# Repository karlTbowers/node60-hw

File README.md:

# Node60 — Automotive 10BASE-T1S Power Distribution Node

Open-hardware six-output automotive power distribution node by DropOut. Each output is a protected smart high-side switch with current and voltage telemetry, reported over a multidrop 10BASE-T1S network.

**Status:** Architecture Rev A, schematic capture starting. Not yet validated hardware.

**Architecture and design documentation:** https://karltbowers.github.io/node60-hw/ (source in [`docs/`](docs/)).

| | |
|---|---|
| MCU | NXP S32K344 |
| Network | Microchip LAN8670 10BASE-T1S PHY (RMII), PLCA follower |
| Outputs | 6 × 10 A target, 3 × TI TPS2HCS08A-Q1 dual smart eFuses |
| Input | 12 V battery-direct, TI LM74910H-Q1 ideal diode + 75 A breaker |
| Tools | KiCad 10, Zephyr RTOS (firmware in a separate repo) |

## Cloning

The DropOut part library is a git submodule, so clone recursively:

```bash
git clone --recursive https://github.com/karlTbowers/node60-hw.git
```

Already cloned without it? Run `git submodule update --init`.

## Workstation

To set up a new Apple-silicon Mac with the whole design environment, run `scripts/setup-workstation.sh`. It installs KiCad 10.0.7, the Homebrew tools, the DropOut repos, KiCadRoutingTools and its Python, then checks that the Mac reproduces the reference judging run. See [`scripts/workstation/README.md`](scripts/workstation/README.md).

## Layout

```
node60.kicad_pro / .kicad_sch / .kicad_pcb    KiCad 10 project; node60.kicad_sch is the root sheet (page 1, index)
sheets/                                       every other schematic sheet, flat (handbook ch. 05)
scripts/check_schematic.py                    CI check: sheet files, page numbers, reference designators
sym-lib-table, fp-lib-table                   point into lib/ — do not use global DropOut tables
lib/dropout-kicad-library/                    submodule: symbols, footprints, 3D models
docs/                                         Starlight documentation site: architecture, calculations, test plans
.github/workflows/ci.yml                      ERC/DRC on every push; fab outputs on tags
.github/workflows/docs.yml                    builds docs/ on PRs; deploys main to GitHub Pages
```

## Library

All parts come from [dropout-kicad-library](https://github.com/karlTbowers/dropout-kicad-library). The project library tables use `${KIPRJMOD}/lib/dropout-kicad-library/...`, so nothing needs to be configured in KiCad's global settings.

Update the library:

```bash
git -C lib/dropout-kicad-library pull origin main
git add lib/dropout-kicad-library
git commit -m "Update DropOut library"
```

## Releases

Board revisions are git tags: `rev-a`, `rev-b`, … Pushing a tag makes CI run ERC and DRC and attach the fabrication package (Gerbers, drill, position file, BOM, schematic PDF) to a GitHub Release.

```bash
git tag rev-a && git push origin rev-a
```

## License

TBD — to be chosen before the first public release.

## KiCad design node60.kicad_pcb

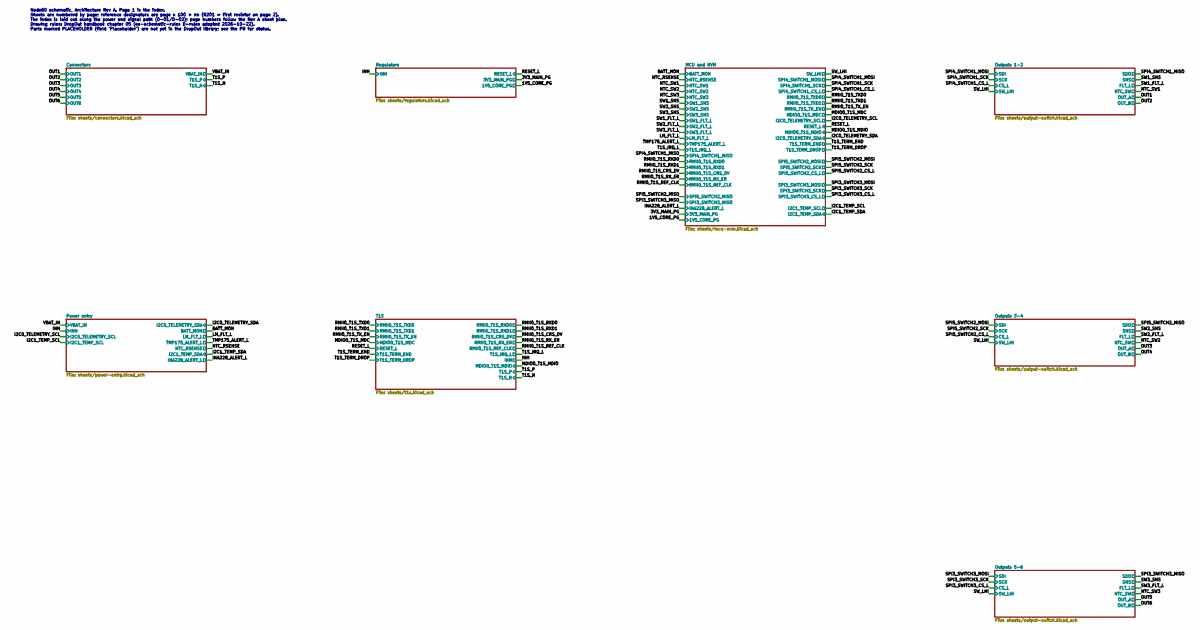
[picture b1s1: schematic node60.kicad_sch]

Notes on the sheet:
Node60 schematic, Architecture Rev A. Page 1 is the index. Sheets are numbered by page; reference designators are page x 100 + nn (R201 = first resistor on page 2). The index is laid out along the power and signal path (D-01/D-02); page numbers follow the Rev A sheet plan. Drawing rules: DropOut ha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

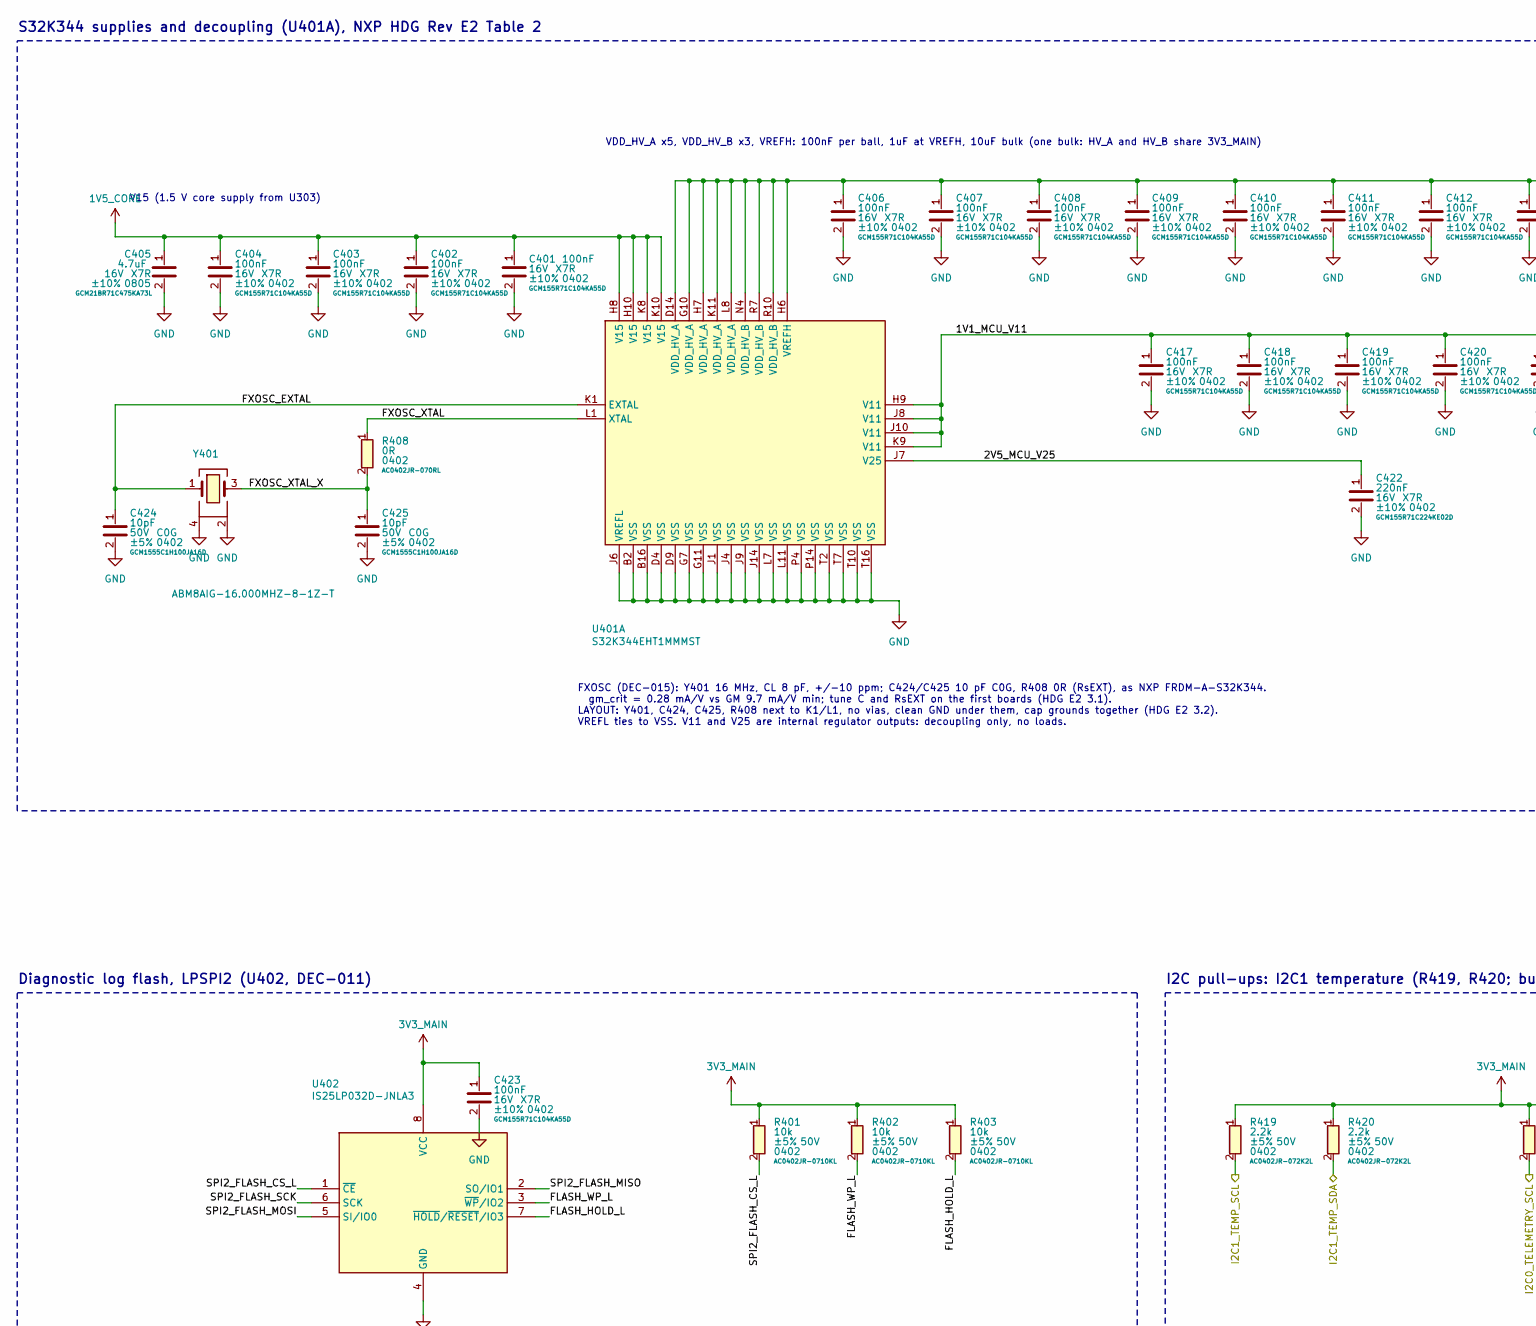
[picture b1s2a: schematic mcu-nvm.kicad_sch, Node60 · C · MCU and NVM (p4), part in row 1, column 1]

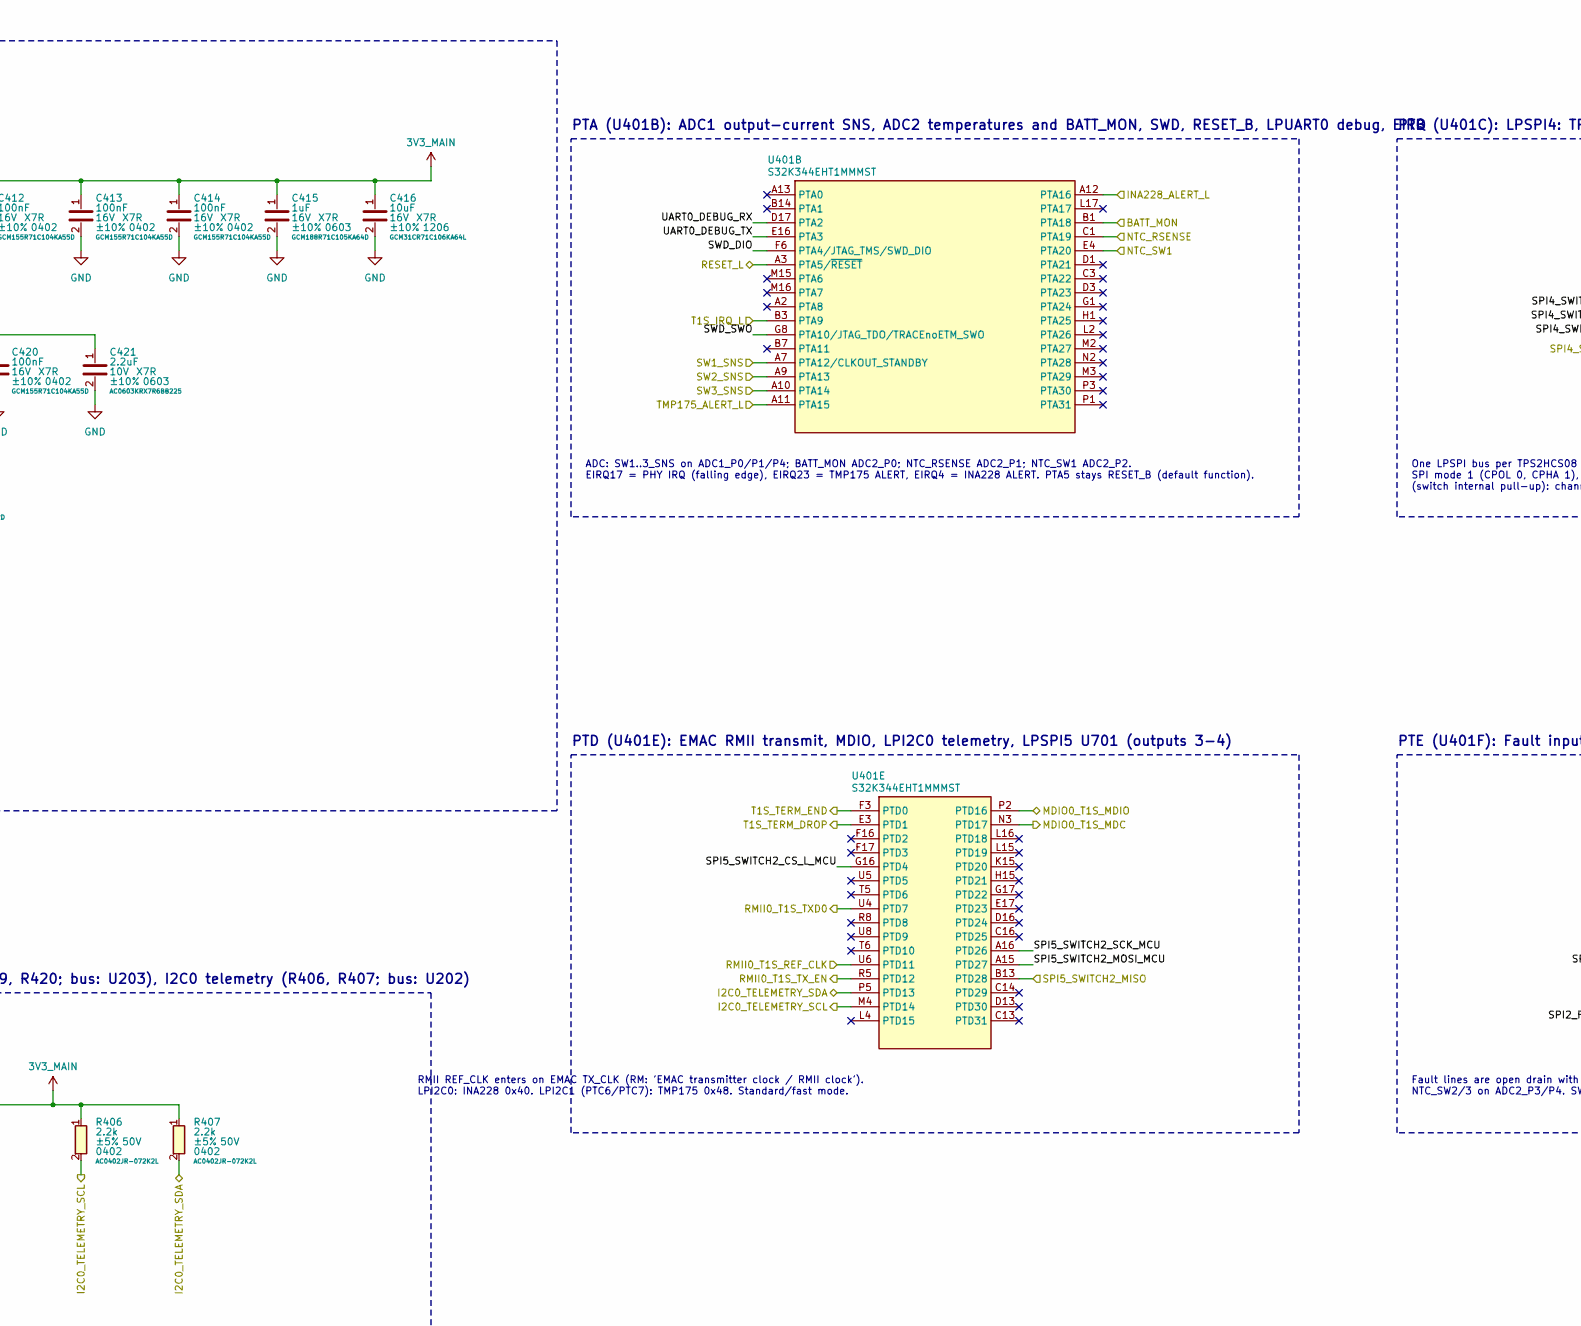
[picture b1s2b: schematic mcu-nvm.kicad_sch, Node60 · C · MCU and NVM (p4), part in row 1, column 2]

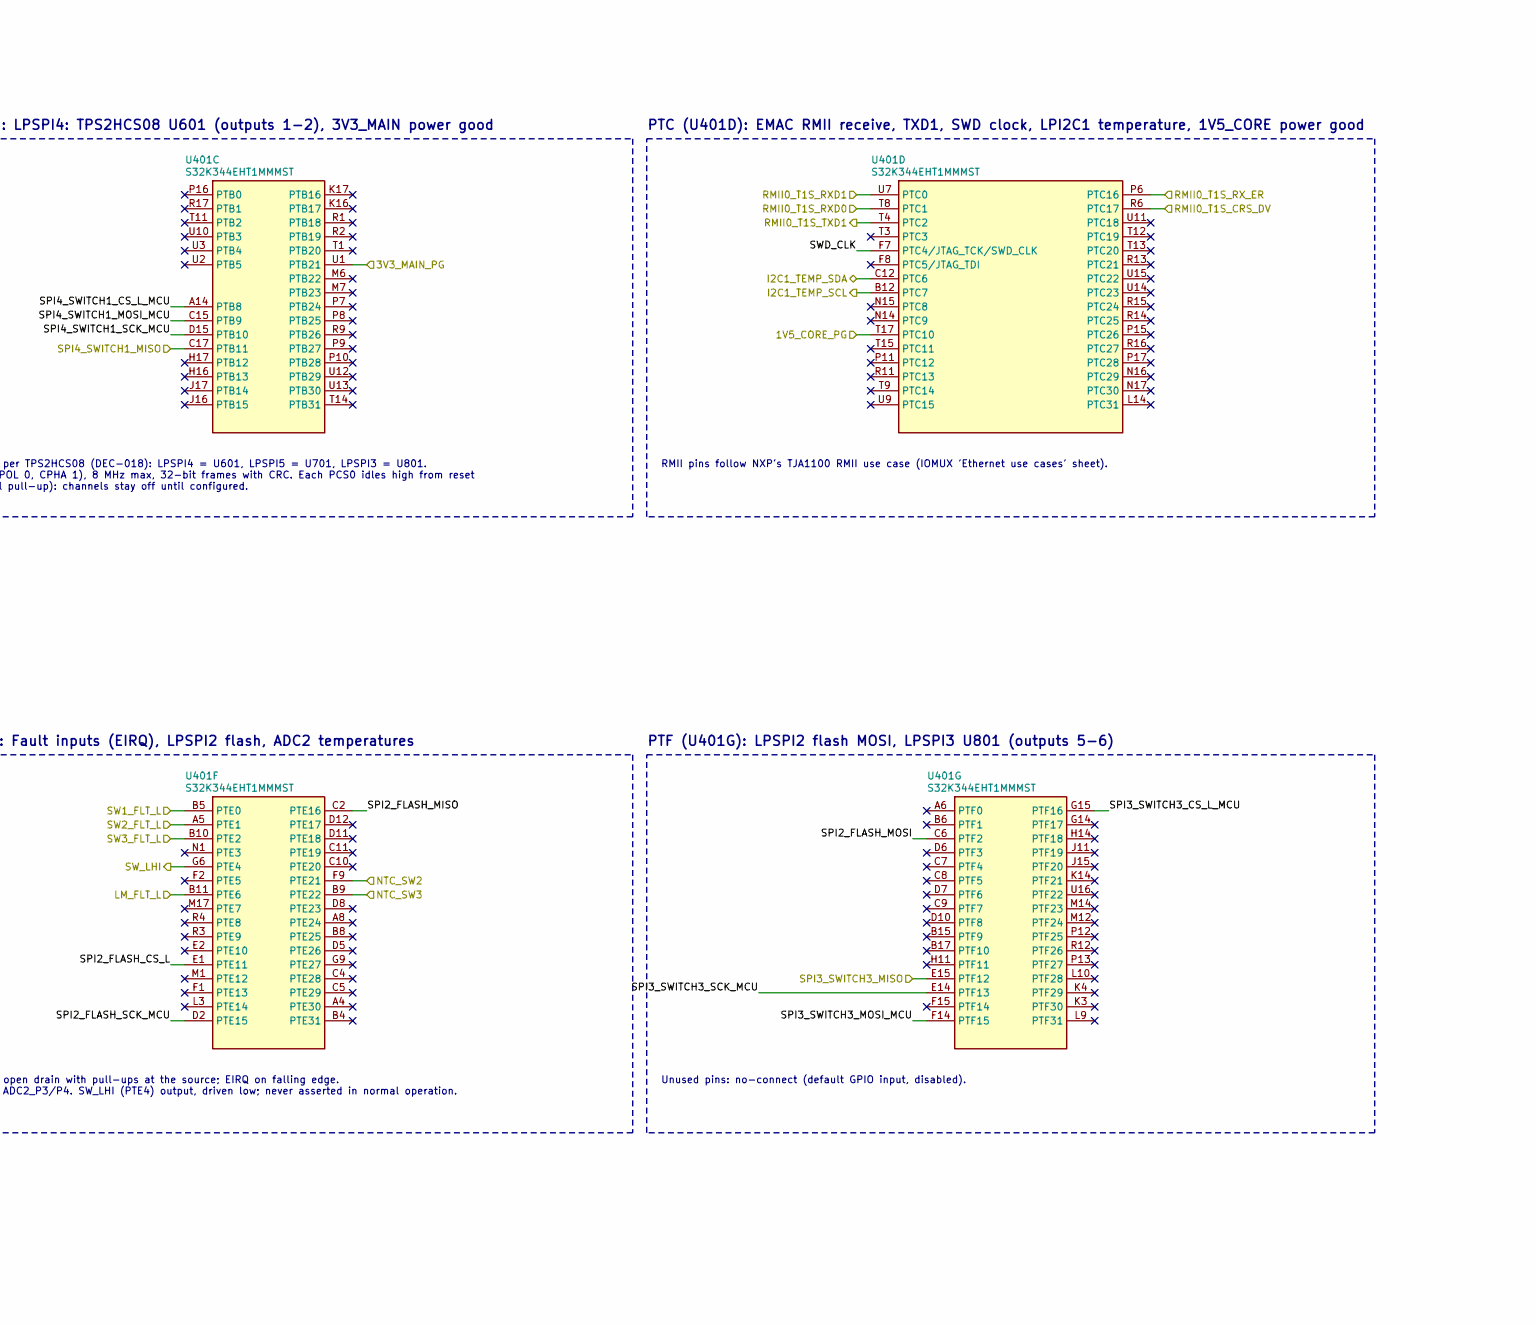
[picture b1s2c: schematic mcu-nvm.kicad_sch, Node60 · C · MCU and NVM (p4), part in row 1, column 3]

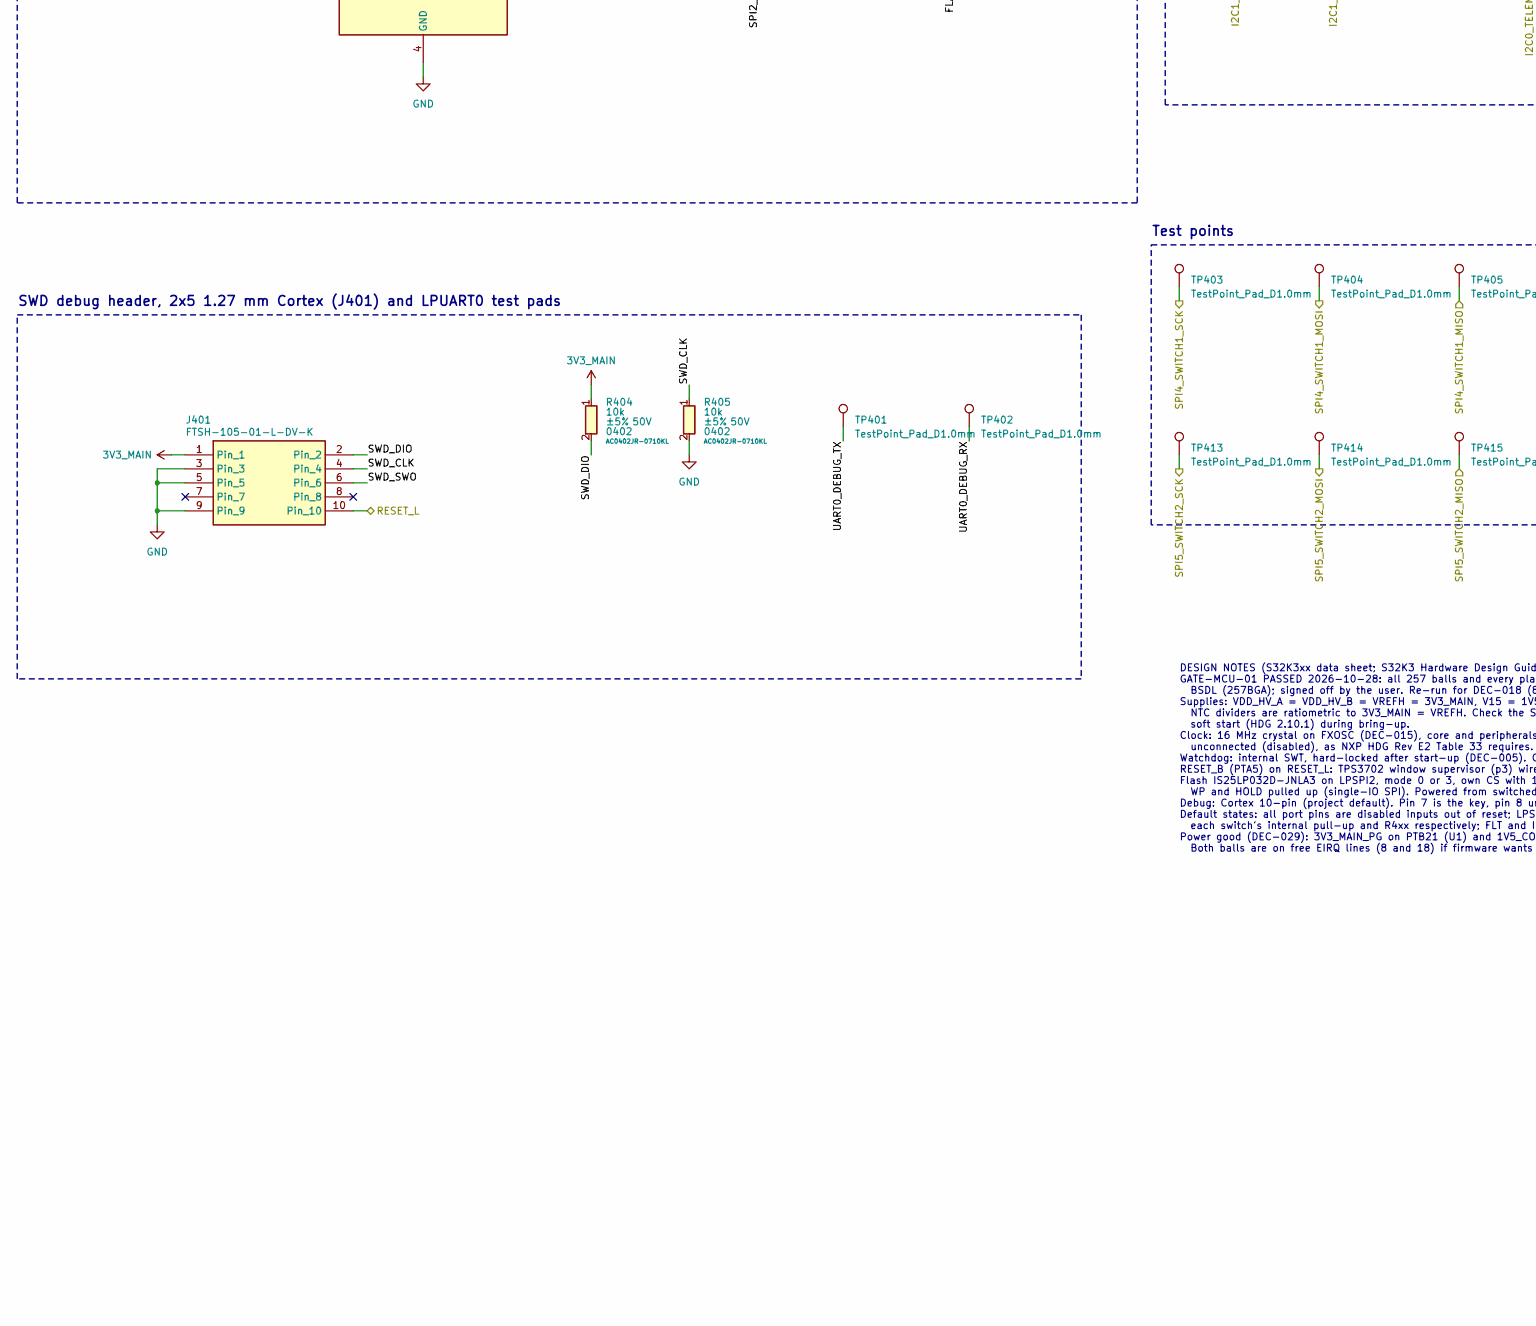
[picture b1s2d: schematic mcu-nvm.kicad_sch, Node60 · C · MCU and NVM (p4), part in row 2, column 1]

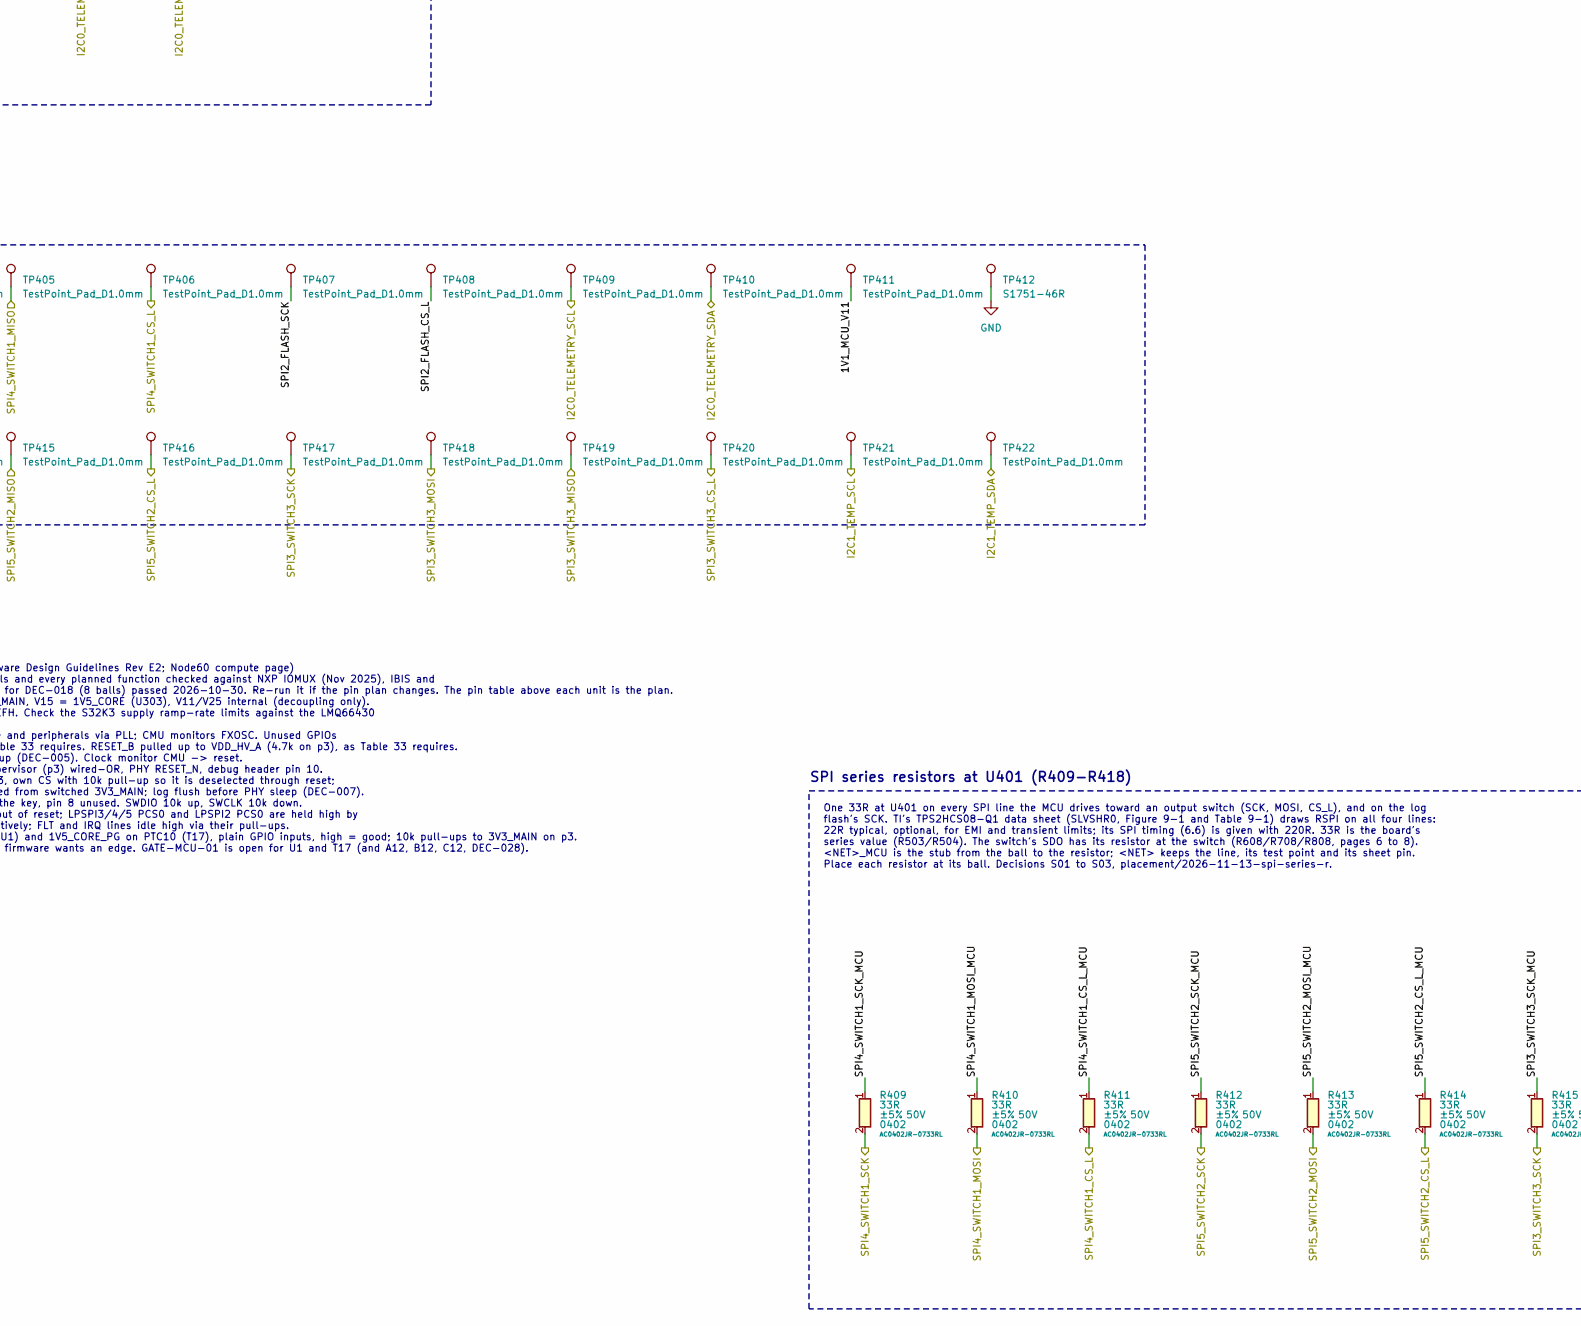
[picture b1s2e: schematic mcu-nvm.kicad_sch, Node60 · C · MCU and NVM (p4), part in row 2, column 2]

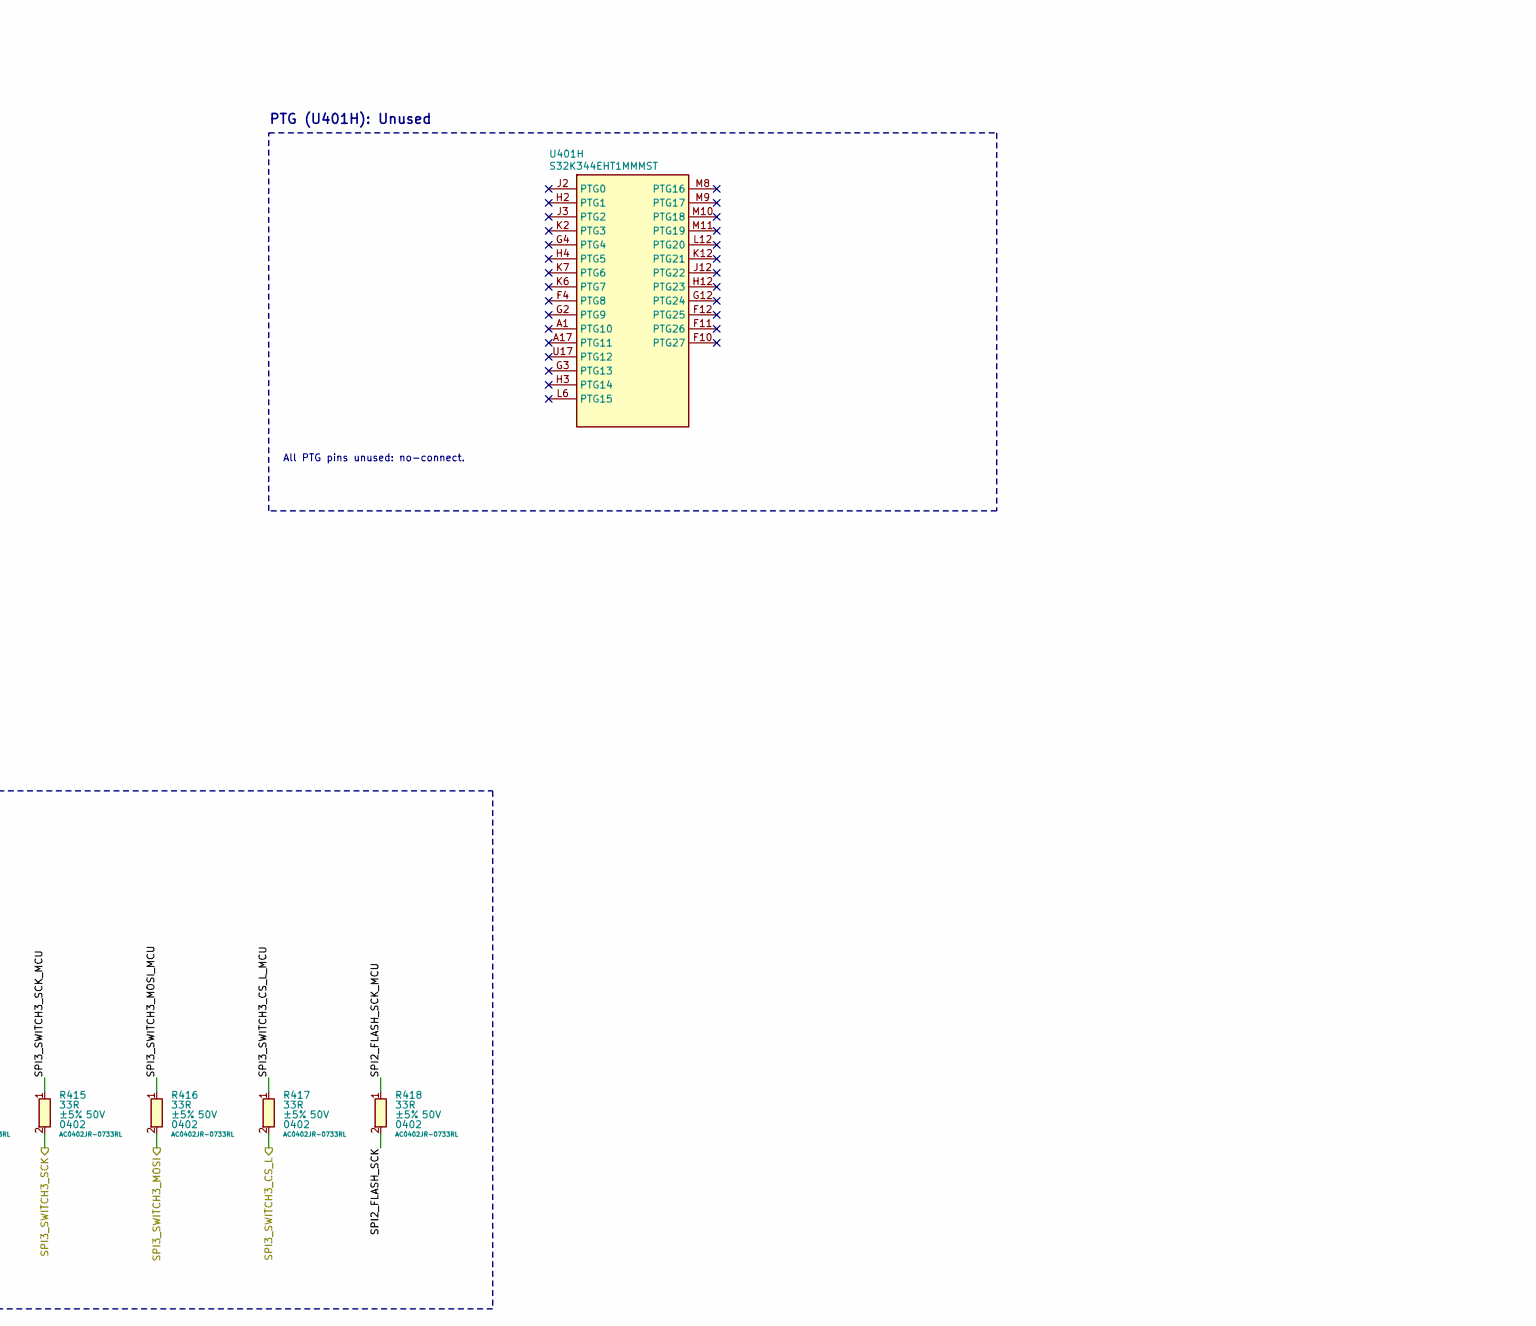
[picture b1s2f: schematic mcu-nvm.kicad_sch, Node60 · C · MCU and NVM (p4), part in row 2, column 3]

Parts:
C401, C402, C403, C404, C406, C407, C408, C409, C410, C411, C412, C413, C414, C417, C418, C419, C420, C423: 100nF; C_0402_1005Metric; Voltage 16V; Tolerance ±10%; MPN GCM155R71C104KA55D; DigiKey_PN 490-4759-1-ND
C405: 4.7uF; C_0805_2012Metric; Voltage 16V; Tolerance ±10%; MPN GCM21BR71C475KA73L; DigiKey_PN 490-5332-1-ND
C415: 1uF; C_0603_1608Metric; Voltage 16V; Tolerance ±10%; MPN GCM188R71C105KA64D; DigiKey_PN 490-5241-1-ND
C416: 10uF; C_1206_3216Metric; Voltage 16V; Tolerance ±10%; MPN GCM31CR71C106KA64L; DigiKey_PN 490-4793-1-ND
C421: 2.2uF; C_0603_1608Metric; Voltage 10V; Tolerance ±10%; MPN AC0603KRX7R6BB225; DigiKey_PN 13-AC0603KRX7R6BB225CT-ND
C422: 220nF; C_0402_1005Metric; Voltage 16V; Tolerance ±10%; MPN GCM155R71C224KE02D; DigiKey_PN 490-10671-1-ND
C424, C425: 10pF; C_0402_1005Metric; Voltage 50V; Tolerance ±5%; MPN GCM1555C1H100JA16D; DigiKey_PN 490-10668-1-ND
J401: FTSH-105-01-L-DV-K; Samtec_FTSH-105-01-x-DV_2x05_P1.27mm_Vertical_SMD; MPN FTSH-105-01-L-DV-K; DigiKey_PN SAM8799-ND
R401, R402, R403, R404, R405: 10k; R_0402_1005Metric; Tolerance ±5%; Voltage 50V; MPN AC0402JR-0710KL; DigiKey_PN YAG3517CT-ND
R406, R407, R419, R420: 2.2k; R_0402_1005Metric; Tolerance ±5%; Voltage 50V; MPN AC0402JR-072K2L; DigiKey_PN YAG3536CT-ND
R408: 0R; R_0402_1005Metric; MPN AC0402JR-070RL; DigiKey_PN 311-0.0LBCT-ND
R409, R410, R411, R412, R413, R414, R415, R416, R417, R418: 33R; R_0402_1005Metric; Tolerance ±5%; Voltage 50V; MPN AC0402JR-0733RL; DigiKey_PN YAG3543CT-ND
TP401, TP402, TP403, TP404, TP405, TP406, TP407, TP408, TP409, TP410, TP411, TP413, TP414, TP415, TP416, TP417, TP418, TP419, TP420, TP421, TP422: TestPoint_Pad_D1.0mm; MPN TestPoint_Pad_D1.0mm
TP412: S1751-46R; TestPoint_Harwin_S1751; MPN S1751-46R; DigiKey_PN 952-1478-1-ND
U401: S32K344EHT1MMMST; NXP_LFBGA-257_14x14mm_Layout17x17_P0.8mm; MPN S32K344EHT1MMMST; DigiKey_PN 568-S32K344EHT1MMMST-ND
U402: IS25LP032D-JNLA3; SOIC-8_3.9x4.9mm_P1.27mm; MPN IS25LP032D-JNLA3; DigiKey_PN 706-IS25LP032D-JNLA3-ND
Y401: ABM8AIG-16.000MHZ-8-1Z-T; Crystal_SMD_NDK_NX3225SA-4Pin_3.2x2.5mm; MPN ABM8AIG-16.000MHZ-8-1Z-T; DigiKey_PN 535-ABM8AIG-16.000MHZ-8-1Z-TCT-ND

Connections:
1V5_CORE: C401.1, C402.1, C403.1, C404.1, C405.1, U401.H8 (V15), U401.H10 (V15), U401.K8 (V15), U401.K10 (V15); also elsewhere on the board
3V3_MAIN: C406.1, C407.1, C408.1, C409.1, C410.1, C411.1, C412.1, C413.1, C414.1, C415.1, C416.1, C423.1, J401.1, R401.1, R402.1, R403.1, R404.1, R406.1, R407.1, R419.1, R420.1, U401.D14 (VDD_HV_A), U401.G10 (VDD_HV_A), U401.H6 (VREFH), U401.H7 (VDD_HV_A), U401.K11 (VDD_HV_A), U401.L8 (VDD_HV_A), U401.N4 (VDD_HV_B), U401.R7 (VDD_HV_B), U401.R10 (VDD_HV_B), U402.8 (VCC); also elsewhere on the board
/1V5_CORE_PG: U401.T17 (PTC10); also elsewhere on the board
/3V3_MAIN_PG: U401.U1 (PTB21); also elsewhere on the board
/BATT_MON: U401.B1 (PTA18); also elsewhere on the board
/I2C0_TELEMETRY_SCL: R406.2, TP409.1 (1_1), U401.M4 (PTD14); also elsewhere on the board
/I2C0_TELEMETRY_SDA: R407.2, TP410.1 (1_1), U401.P5 (PTD13); also elsewhere on the board
/I2C1_TEMP_SCL: R419.2, TP421.1 (1_1), U401.B12 (PTC7); also elsewhere on the board
/I2C1_TEMP_SDA: R420.2, TP422.1 (1_1), U401.C12 (PTC6); also elsewhere on the board
/INA228_ALERT_L: U401.A12 (PTA16); also elsewhere on the board
/LM_FLT_L: U401.B11 (PTE6); also elsewhere on the board
/MCU and NVM/1V1_MCU_V11: C417.1, C418.1, C419.1, C420.1, C421.1, TP411.1 (1_1), U401.H9 (V11), U401.J8 (V11), U401.J10 (V11), U401.K9 (V11)
/MCU and NVM/2V5_MCU_V25: C422.1, U401.J7 (V25)
/MCU and NVM/FLASH_HOLD_L: R403.2, U402.7 (~HOLD/~RESET/IO3)
/MCU and NVM/FLASH_WP_L: R402.2, U402.3 (~WP/IO2)
/MCU and NVM/FXOSC_EXTAL: C424.1, U401.K1 (EXTAL), Y401.1
/MCU and NVM/FXOSC_XTAL: R408.1, U401.L1 (XTAL)
/MCU and NVM/FXOSC_XTAL_X: C425.1, R408.2, Y401.3
/MCU and NVM/SPI2_FLASH_CS_L: R401.2, TP408.1 (1_1), U401.E1 (PTE11), U402.1 (~CE)
/MCU and NVM/SPI2_FLASH_MISO: U401.C2 (PTE16), U402.2 (SO/IO1)
/MCU and NVM/SPI2_FLASH_MOSI: U401.C6 (PTF2), U402.5 (SI/IO0)
/MCU and NVM/SPI2_FLASH_SCK: R418.2, TP407.1 (1_1), U402.6 (SCK)
/MCU and NVM/SPI2_FLASH_SCK_MCU: R418.1, U401.D2 (PTE15)
/MCU and NVM/SPI3_SWITCH3_CS_L_MCU: R417.1, U401.G15 (PTF16)
/MCU and NVM/SPI3_SWITCH3_MOSI_MCU: R416.1, U401.F14 (PTF15)
/MCU and NVM/SPI3_SWITCH3_SCK_MCU: R415.1, U401.E14 (PTF13)
/MCU and NVM/SPI4_SWITCH1_CS_L_MCU: R411.1, U401.A14 (PTB8)
/MCU and NVM/SPI4_SWITCH1_MOSI_MCU: R410.1, U401.C15 (PTB9)
/MCU and NVM/SPI4_SWITCH1_SCK_MCU: R409.1, U401.D15 (PTB10)
/MCU and NVM/SPI5_SWITCH2_CS_L_MCU: R414.1, U401.G16 (PTD4)
/MCU and NVM/SPI5_SWITCH2_MOSI_MCU: R413.1, U401.A15 (PTD27)
/MCU and NVM/SPI5_SWITCH2_SCK_MCU: R412.1, U401.A16 (PTD26)
/MCU and NVM/SWD_CLK: J401.4, R405.1, U401.F7 (PTC4/JTAG_TCK/SWD_CLK)
/MCU and NVM/SWD_DIO: J401.2, R404.2, U401.F6 (PTA4/JTAG_TMS/SWD_DIO)
/MCU and NVM/SWD_SWO: J401.6, U401.G8 (PTA10/JTAG_TDO/TRACEnoETM_SWO)
/MCU and NVM/UART0_DEBUG_RX: TP402.1 (1_1), U401.D17 (PTA2)
/MCU and NVM/UART0_DEBUG_TX: TP401.1 (1_1), U401.E16 (PTA3)
/MDIO0_T1S_MDC: U401.N3 (PTD17); also elsewhere on the board
/MDIO0_T1S_MDIO: U401.P2 (PTD16); also elsewhere on the board
/NTC_RSENSE: U401.C1 (PTA19); also elsewhere on the board
/NTC_SW1: U401.E4 (PTA20); also elsewhere on the board
/NTC_SW2: U401.F9 (PTE21); also elsewhere on the board
/NTC_SW3: U401.B9 (PTE22); also elsewhere on the board
/RESET_L: J401.10, U401.A3 (PTA5/~RESET); also elsewhere on the board
/RMII0_T1S_CRS_DV: U401.R6 (PTC17); also elsewhere on the board
/RMII0_T1S_REF_CLK: U401.U6 (PTD11); also elsewhere on the board
/RMII0_T1S_RXD0: U401.T8 (PTC1); also elsewhere on the board
/RMII0_T1S_RXD1: U401.U7 (PTC0); also elsewhere on the board
/RMII0_T1S_RX_ER: U401.P6 (PTC16); also elsewhere on the board
/RMII0_T1S_TXD0: U401.U4 (PTD7); also elsewhere on the board
/RMII0_T1S_TXD1: U401.T4 (PTC2); also elsewhere on the board
/RMII0_T1S_TX_EN: U401.R5 (PTD12); also elsewhere on the board
/SPI3_SWITCH3_CS_L: R417.2, TP420.1 (1_1); also elsewhere on the board
/SPI3_SWITCH3_MISO: TP419.1 (1_1), U401.E15 (PTF12); also elsewhere on the board
/SPI3_SWITCH3_MOSI: R416.2, TP418.1 (1_1); also elsewhere on the board
/SPI3_SWITCH3_SCK: R415.2, TP417.1 (1_1); also elsewhere on the board
/SPI4_SWITCH1_CS_L: R411.2, TP406.1 (1_1); also elsewhere on the board
/SPI4_SWITCH1_MISO: TP405.1 (1_1), U401.C17 (PTB11); also elsewhere on the board
/SPI4_SWITCH1_MOSI: R410.2, TP404.1 (1_1); also elsewhere on the board
/SPI4_SWITCH1_SCK: R409.2, TP403.1 (1_1); also elsewhere on the board
/SPI5_SWITCH2_CS_L: R414.2, TP416.1 (1_1); also elsewhere on the board
/SPI5_SWITCH2_MISO: TP415.1 (1_1), U401.B13 (PTD28); also elsewhere on the board
/SPI5_SWITCH2_MOSI: R413.2, TP414.1 (1_1); also elsewhere on the board
/SPI5_SWITCH2_SCK: R412.2, TP413.1 (1_1); also elsewhere on the board
/SW1_FLT_L: U401.B5 (PTE0); also elsewhere on the board
/SW1_SNS: U401.A7 (PTA12/CLKOUT_STANDBY); also elsewhere on the board
/SW2_FLT_L: U401.A5 (PTE1); also elsewhere on the board
/SW2_SNS: U401.A9 (PTA13); also elsewhere on the board
/SW3_FLT_L: U401.B10 (PTE2); also elsewhere on the board
/SW3_SNS: U401.A10 (PTA14); also elsewhere on the board
/SW_LHI: U401.G6 (PTE4); also elsewhere on the board
/T1S_IRQ_L: U401.B3 (PTA9); also elsewhere on the board
/T1S_TERM_DROP: U401.E3 (PTD1); also elsewhere on the board
/T1S_TERM_END: U401.F3 (PTD0); also elsewhere on the board
/TMP175_ALERT_L: U401.A11 (PTA15); also elsewhere on the board
GND: C401.2, C402.2, C403.2, C404.2, C405.2, C406.2, C407.2, C408.2, C409.2, C410.2, C411.2, C412.2, C413.2, C414.2, C415.2, C416.2, C417.2, C418.2, C419.2, C420.2, C421.2, C422.2, C423.2, C424.2, C425.2, J401.3, J401.5, J401.9, R405.2, TP412.1 (1_1), U401.B2 (VSS), U401.B16 (VSS), U401.D4 (VSS), U401.D9 (VSS), U401.G7 (VSS), U401.G11 (VSS), U401.J1 (VSS), U401.J4 (VSS), U401.J6 (VREFL), U401.J9 (VSS), U401.J14 (VSS), U401.L7 (VSS), U401.L11 (VSS), U401.P4 (VSS), U401.P14 (VSS), U401.T2 (VSS), U401.T7 (VSS), U401.T10 (VSS), U401.T16 (VSS), U402.4 (GND), Y401.2 (G), Y401.4 (G); also elsewhere on the board

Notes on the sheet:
PTF (U401G): LPSPI2 flash MOSI, LPSPI3 U801 (outputs 5-6)
PTC (U401D): EMAC RMII receive, TXD1, SWD clock, LPI2C1 temperature, 1V5_CORE power good
RMII pins follow NXP's TJA1100 RMII use case (IOMUX 'Ethernet use cases' sheet).
PTD (U401E): EMAC RMII transmit, MDIO, LPI2C0 telemetry, LPSPI5 U701 (outputs 3-4)
VDD_HV_A x5, VDD_HV_B x3, VREFH: 100nF per ball, 1uF at VREFH, 10uF bulk (one bulk: HV_A and HV_B share 3V3_MAIN)
V15 (1.5 V core supply from U303)
SPI series resistors at U401 (R409-R418)
Unused pins: no-connect (default GPIO input, disabled).
Diagnostic log flash, LPSPI2 (U402, DEC-011)
DESIGN NOTES (S32K3xx data sheet; S32K3 Hardware Design Guidelines Rev E2; Node60 compute page) GATE-MCU-01 PASSED 2026-10-28: all 257 balls and every planned function checked against NXP IOMUX (Nov 2025), IBIS and BSDL (257BGA); signed off by the user. Re-run for DEC-018 (8 balls) passed 2026-10-3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
RMII REF_CLK enters on EMAC TX_CLK (RM: 'EMAC transmitter clock / RMII clock'). LPI2C0: INA228 0x40. LPI2C1 (PTC6/PTC7): TMP175 0x48. Standard/fast mode.
One LPSPI bus per TPS2HCS08 (DEC-018): LPSPI4 = U601, LPSPI5 = U701, LPSPI3 = U801. SPI mode 1 (CPOL 0, CPHA 1), 8 MHz max, 32-bit frames with CRC. Each PCS0 idles high from reset (switch internal pull-up): channels stay off until configured.
I2C pull-ups: I2C1 temperature (R419, R420; bus: U203), I2C0 telemetry (R406, R407; bus: U202)
PTB (U401C): LPSPI4: TPS2HCS08 U601 (outputs 1-2), 3V3_MAIN power good
PTG (U401H): Unused
Fault lines are open drain with pull-ups at the source; EIRQ on falling edge. NTC_SW2/3 on ADC2_P3/P4. SW_LHI (PTE4) output, driven low; never asserted in normal operation.
One 33R at U401 on every SPI line the MCU drives toward an output switch (SCK, MOSI, CS_L), and on the log flash's SCK. TI's TPS2HCS08-Q1 data sheet (SLVSHR0, Figure 9-1 and Table 9-1) draws RSPI on all four lines: 22R typical, optional, for EMI and transient limits; its SPI timing (6.6) is given w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
S32K344 supplies and decoupling (U401A), NXP HDG Rev E2 Table 2
FXOSC (DEC-015): Y401 16 MHz, CL 8 pF, +/-10 ppm; C424/C425 10 pF C0G, R408 0R (RsEXT), as NXP FRDM-A-S32K344. gm_crit = 0.28 mA/V vs GM 9.7 mA/V min; tune C and RsEXT on the first boards (HDG E2 3.1). LAYOUT: Y401, C424, C425, R408 next to K1/L1, no vias, clean GND under them, cap grounds together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
Test points
ADC: SW1..3_SNS on ADC1_P0/P1/P4; BATT_MON ADC2_P0; NTC_RSENSE ADC2_P1; NTC_SW1 ADC2_P2. EIRQ17 = PHY IRQ (falling edge), EIRQ23 = TMP175 ALERT, EIRQ4 = INA228 ALERT. PTA5 stays RESET_B (default function).
PTA (U401B): ADC1 output-current SNS, ADC2 temperatures and BATT_MON, SWD, RESET_B, LPUART0 debug, EIRQ
All PTG pins unused: no-connect.
SWD debug header, 2x5 1.27 mm Cortex (J401) and LPUART0 test pads
PTE (U401F): Fault inputs (EIRQ), LPSPI2 flash, ADC2 temperatures
